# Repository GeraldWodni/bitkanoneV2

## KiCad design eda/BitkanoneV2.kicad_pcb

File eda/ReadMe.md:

EDA
===

KiCad 5 is required to work on this project properly. I have no experience with EDA files in a repo, and how well they merge, so it might be better to request changes in an issue or ask for exclusive access so we do not destroy each others changes ;)

Bus
---

As Ulli suggested, the Bus should be CAN bus. As the schedule is tight a backup plan exists in the schematics, which allows to Bridge the CAN driver and use I2C directly. Note, however that in that case only 1 PCB should have it's pullups populated, as they are on 1k8 which will allow high speeds at 3mA low source current.

https://cdn-reichelt.de/documents/datenblatt/A200/MCP2551_MIC.pdf

Sensor
------

Martin found a nice PCB which holds the BMP280 suggested by Erich and Bernd as well as a Gyro and more. This is called a 10DOF, and can be sourced more or less easily. Boards differ in pin count, but the first 4 pins are always:

1. VIN (wird mit 3.3V gespeist)
2. GND
3. 3V3 (out)
4. SDA
5. SCL

The other pins are ignored.
Ebay: Eckstein

https://store.invensense.com/datasheets/invensense/MPU-6050_DataSheet_V3%204.pdf
https://www.ebay.de/itm/10DOF-Lsm303d-L3gd20-BMP180-Breakout-Modul-Beschleunigungsmesser-Kompass/253091721043?hash=item3aed712f53:g:O0UAAOSw~I5ZjqvM:rk:18:pf:0
https://www.ebay.de/itm/New-SPI-IIC-MPU-9250-MS5611-High-Precision-9-Axis-10DOF-Altitude-sensor-Module/272672204397?hash=item3f7c87a66d:g:fSAAAOSwn-tZGX4T:rk:14:pf:0
https://www.ebay.de/itm/GY-87-10DOF-3-Achsen-Gyroskop-Accelerometer-Sensor-Modul-SE01006/281460524502?hash=item41885ac5d6:g:vKwAAOSwhnlb~pYd:rk:13:pf:0
https://www.reichelt.at/arduino-grove-sensor-imu-10dof-v2-0-grv-imu-10dof-v2-p243392.html?PROVID=2788&gclid=EAIaIQobChMIuNSy9rWQ3wIVhOmaCh0uWwYPEAQYAyABEgIEOfD_BwE&&r=1
https://www.banggood.com/GY-91-MPU9250-BMP280-10DOF-Acceleration-Gyroscope-Compass-Nine-Shaft-Sensor-Module-p-1129541.html?rmmds=search&cur_warehouse=CN

10DOF schematics
http://kom.aau.dk/~jdn/edu/doc/arduino/sensors/gy80gy87gy88/gy87sch.jpg

Motors
------

As there is so little time and much room for error, there is a Motor-Daughterboard connector which will eventually allow to run DC motors via L293D. It's first job is to run Servos instead and allow a Pan/Tilt movement of the Board.

Power
-----

Stand alone boards can be powered via a beefy USB, or can disconnect the solder jumper and supply external Power via X101

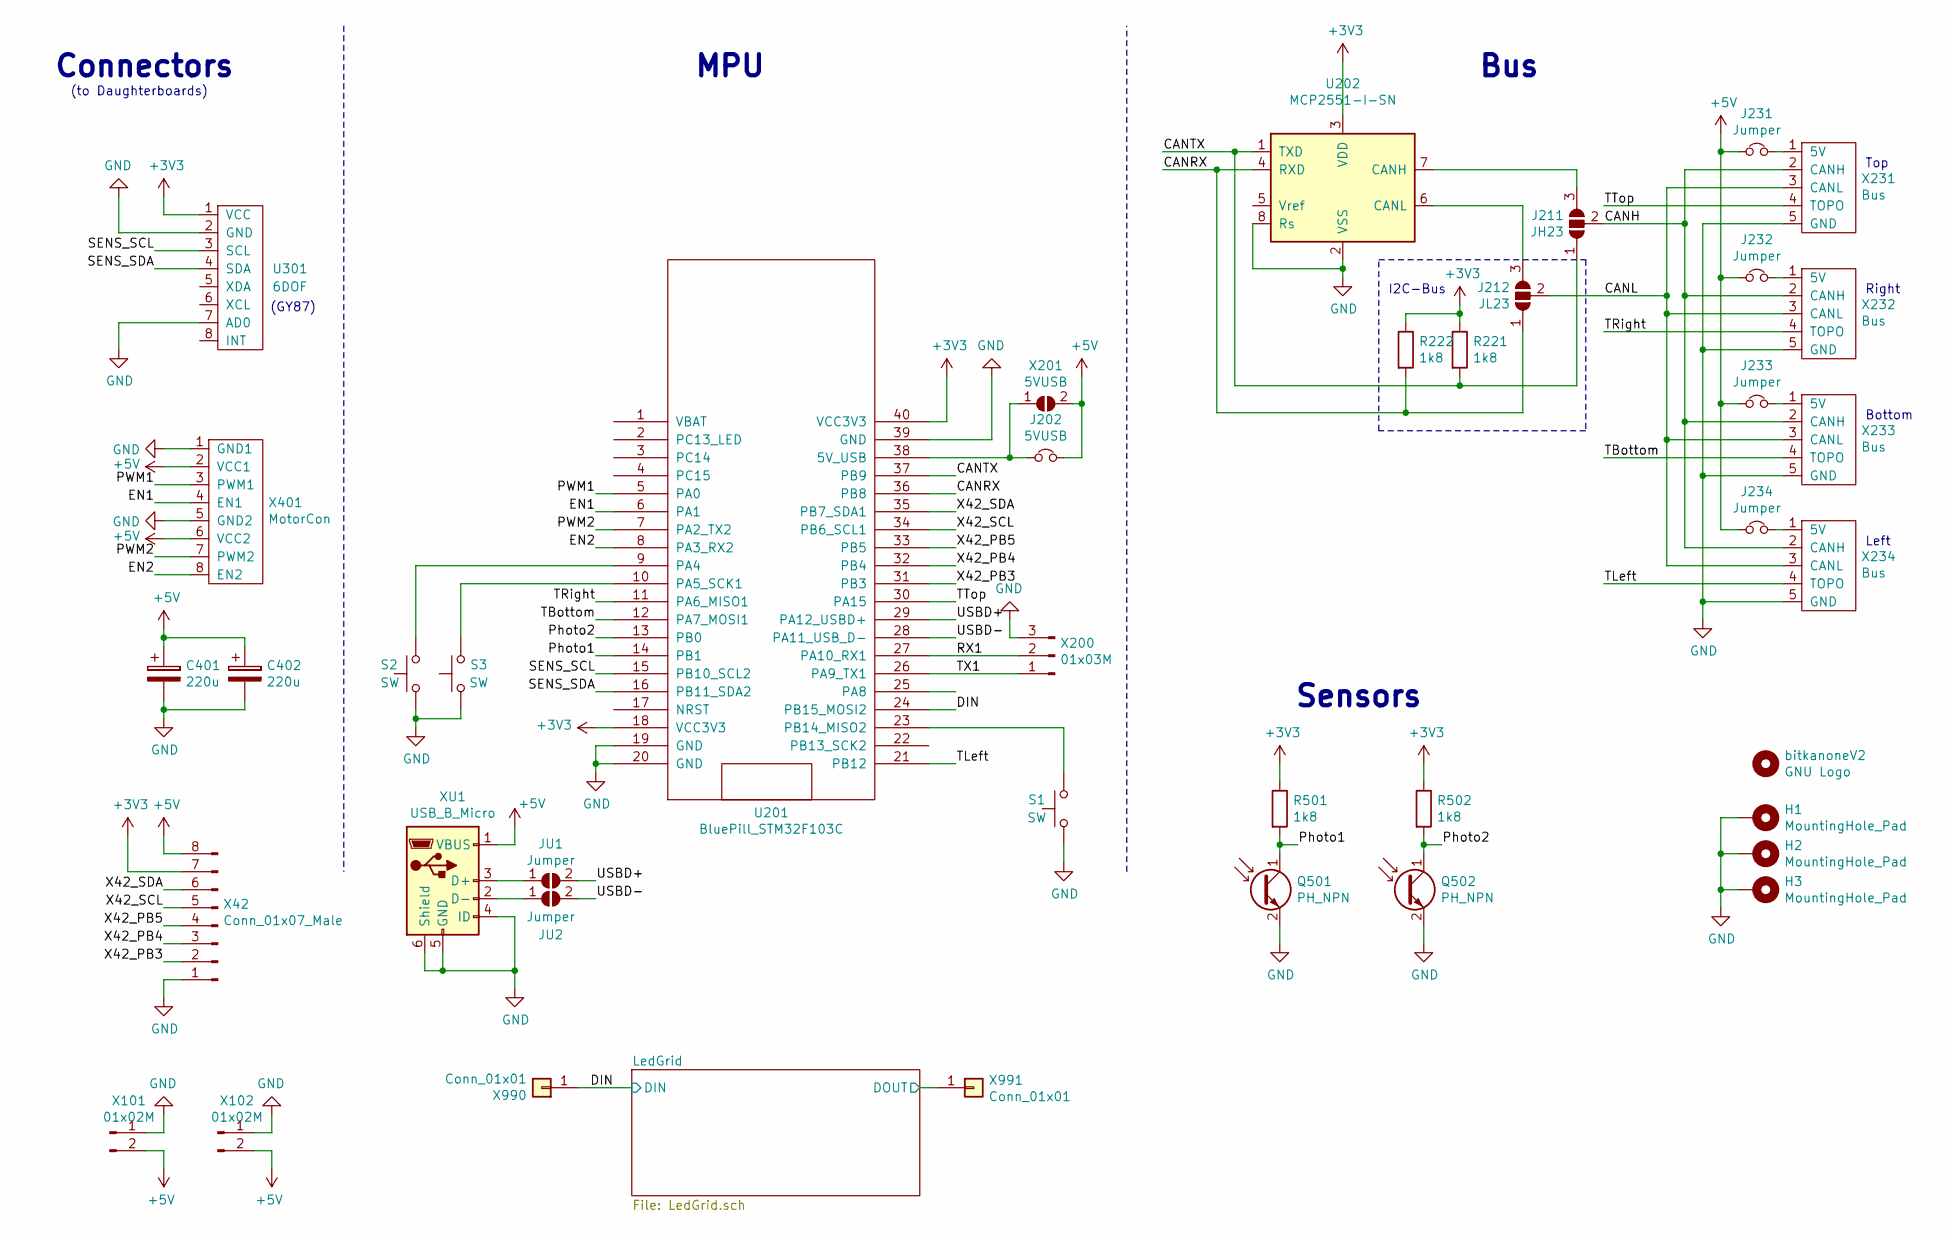
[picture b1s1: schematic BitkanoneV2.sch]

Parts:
C401, C402: 220u; CP_Elec_6.3x5.3
H1, H2, H3: MountingHole_Pad; MountingHole_3.2mm_M3_Pad_Via
J202: 5VUSB; PinSocket_1x02_P2.54mm_Vertical
J211: JH23; SolderJumper-3_P1.3mm_Open_RoundedPad1.0x1.5mm_NumberLabels
J212: JL23; SolderJumper-3_P1.3mm_Open_RoundedPad1.0x1.5mm_NumberLabels
J231, J232, J233, J234: Jumper; SolderJumper-2_P1.3mm_Open_Pad1.0x1.5mm
JU1, JU2: Jumper; SolderJumper-2_P1.3mm_Open_RoundedPad1.0x1.5mm
Q501, Q502: PH_NPN; LED_D3.0mm
R221, R222, R501, R502: 1k8; R_0603_1608Metric_Pad1.05x0.95mm_HandSolder
S1, S2, S3: SW; SW_SPST_FSMSM
U201: BluePill_STM32F103C; BluePill_STM32F103C_Center_NoPROG
U202: MCP2551-I-SN; SOIC-8_3.9x4.9mm_P1.27mm
U301: 6DOF; PinSocket_1x08_P2.54mm_Vertical
X42: Conn_01x07_Male; PinSocket_1x08_P2.54mm_Vertical
X101, X102: 01x02M; PinHeader_1x02_P2.54mm_Vertical
X200: 01x03M; PinHeader_1x03_P2.54mm_Vertical
X201: 5VUSB; SolderJumper-2_P1.3mm_Open_Pad1.0x1.5mm
X231, X232, X233, X234: Bus; PinSocket_1x05_P2.54mm_Vertical
X401: MotorCon; PinSocket_1x08_P2.54mm_Vertical
X990, X991: Conn_01x01; PinHeader_1x01_P2.54mm_Vertical
XU1: USB_B_Micro; USB_Micro-B_Molex-105017-0001
bitkanoneV2: GNU Logo; Symbol_GNU-Logo_SilkscreenTop

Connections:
+3V3: R221.1, R222.1, R501.1, R502.1, U201.18 (VCC3V3), U201.40 (VCC3V3), U202.3 (VDD), U301.1 (VCC), X42.7
+5V: C401.1, C402.1, J202.2, J231.1, J232.1, J233.1, J234.1, X42.8, X101.2, X102.2, X201.2 (B), X401.2 (VCC1), X401.6 (VCC2), XU1.1 (VBUS); also elsewhere on the board
/CANH: J211.2 (C), X231.2 (CANH), X232.2 (CANH), X233.2 (CANH), X234.2 (CANH)
/CANL: J212.2 (C), X231.3 (CANL), X232.3 (CANL), X233.3 (CANL), X234.3 (CANL)
/CANRX: J212.1 (A), R222.2, U201.36 (PB8), U202.4 (RXD)
/CANTX: J211.1 (A), R221.2, U201.37 (PB9), U202.1 (TXD)
/DIN: U201.24 (PB15_MOSI2), X990.1; also elsewhere on the board
/EN1: U201.6 (PA1), X401.4 (EN1)
/EN2: U201.8 (PA3_RX2), X401.8 (EN2)
/LedGrid/DOUT: X991.1; also elsewhere on the board
/PWM1: U201.5 (PA0), X401.3 (PWM1)
/PWM2: U201.7 (PA2_TX2), X401.7 (PWM2)
/Photo1: Q501.1 (C), R501.2, U201.14 (PB1)
/Photo2: Q502.1 (C), R502.2, U201.13 (PB0)
/RX1: U201.27 (PA10_RX1), X200.2
/SENS_SCL: U201.15 (PB10_SCL2), U301.3 (SCL)
/SENS_SDA: U201.16 (PB11_SDA2), U301.4 (SDA)
/TBottom: U201.12 (PA7_MOSI1), X233.4 (TOPO)
/TLeft: U201.21 (PB12), X234.4 (TOPO)
/TRight: U201.11 (PA6_MISO1), X232.4 (TOPO)
/TTop: U201.30 (PA15), X231.4 (TOPO)
/TX1: U201.26 (PA9_TX1), X200.1
/USBD+: JU1.2 (B), U201.29 (PA12_USBD+)
/USBD-: JU2.2 (B), U201.28 (PA11_USB_D-)
/X42_PB3: U201.31 (PB3), X42.2
/X42_PB4: U201.32 (PB4), X42.3
/X42_PB5: U201.33 (PB5), X42.4
/X42_SCL: U201.34 (PB6_SCL1), X42.5
/X42_SDA: U201.35 (PB7_SDA1), X42.6
GND: C401.2, C402.2, H1.1, H2.1, H3.1, Q501.2 (E), Q502.2 (E), S1.1, S2.1, S3.1, U201.19 (GND), U201.20 (GND), U201.39 (GND), U202.2 (VSS), U202.8 (Rs), U301.2 (GND), U301.7 (AD0), X42.1, X101.1, X102.1, X200.3, X231.5 (GND), X232.5 (GND), X233.5 (GND), X234.5 (GND), X401.1 (GND1), X401.5 (GND2), XU1.4 (ID), XU1.5 (GND), XU1.6 (Shield); also elsewhere on the board
unnamed: J202.1, U201.38 (5V_USB), X201.1 (A)
unnamed: J211.3 (B), U202.7 (CANH)
unnamed: J212.3 (B), U202.6 (CANL)
unnamed: J231.2, X231.1 (5V)
unnamed: J232.2, X232.1 (5V)
unnamed: J233.2, X233.1 (5V)
unnamed: J234.2, X234.1 (5V)
unnamed: JU1.1 (A), XU1.3 (D+)
unnamed: JU2.1 (A), XU1.2 (D-)
unnamed: S1.2, U201.23 (PB14_MISO2)
unnamed: S2.2, U201.9 (PA4)
unnamed: S3.2, U201.10 (PA5_SCK1)

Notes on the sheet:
I2C-Bus
Bus
MPU
Connectors
(to Daughterboards)
(GY87)
Left
Bottom
Right
Top
Sensors

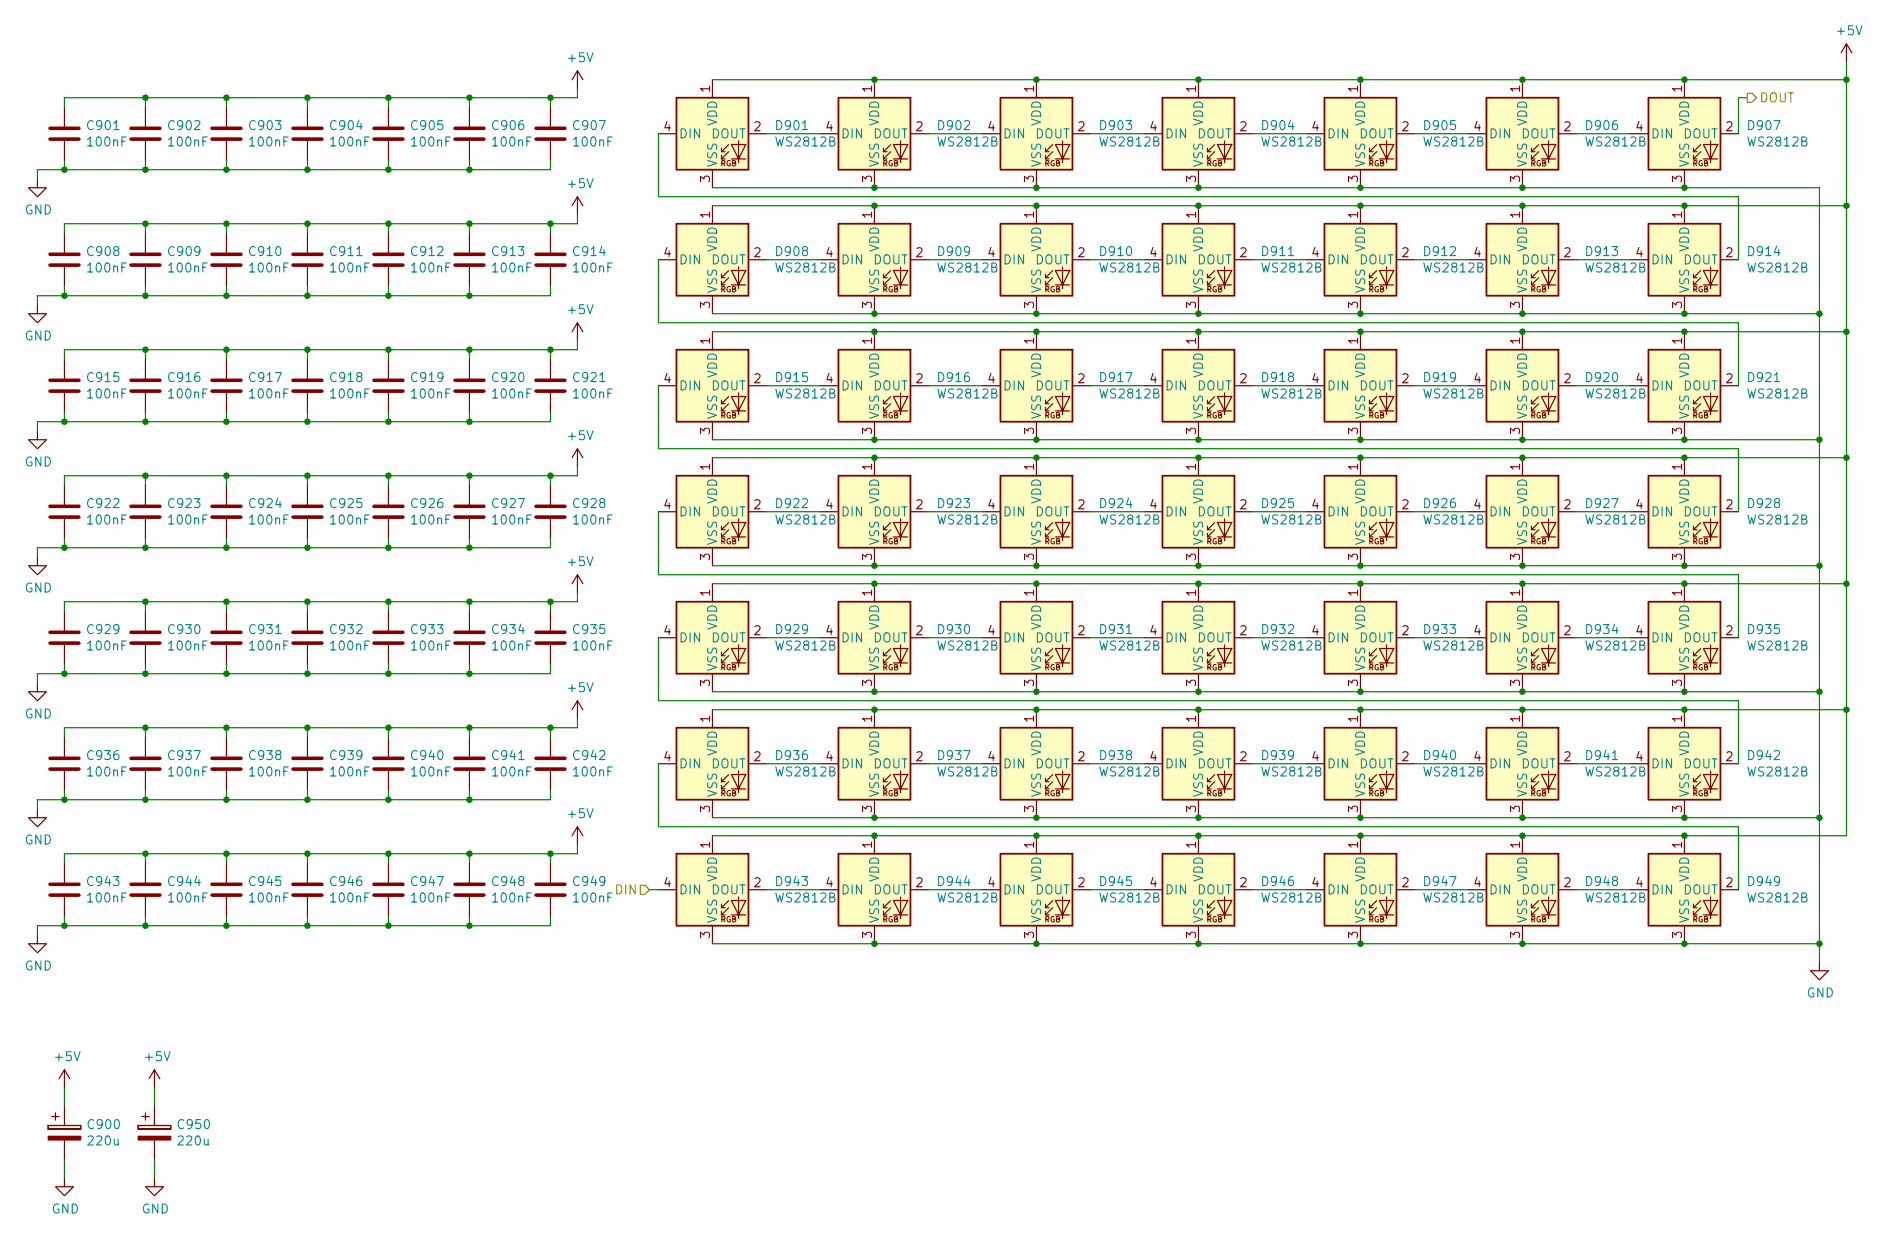
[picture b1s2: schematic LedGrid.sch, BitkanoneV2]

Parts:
C900, C950: 220u; CP_Elec_6.3x5.3
C901, C902, C903, C904, C905, C906, C907, C908, C909, C910, C911, C912, C913, C914, C915, C916, C917, C918, C919, C920, C921, C922, C923, C924, C925, C926, C927, C928, C929, C930, C931, C932, C933, C934, C935, C936, C937, C938, C939, C940, C941, C942, C943, C944, C945, C946, C947, C948, C949: 100nF; C_0603_1608Metric
D901, D902, D903, D904, D905, D906, D907, D908, D909, D910, D911, D912, D913, D914, D915, D916, D917, D918, D919, D920, D921, D922, D923, D924, D925, D926, D927, D928, D929, D930, D931, D932, D933, D934, D935, D936, D937, D938, D939, D940, D941, D942, D943, D944, D945, D946, D947, D948, D949: WS2812B; LED_WS2812B_PLCC4_5.0x5.0mm_P3.2mm

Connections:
+5V: C900.1, C901.1, C902.1, C903.1, C904.1, C905.1, C906.1, C907.1, C908.1, C909.1, C910.1, C911.1, C912.1, C913.1, C914.1, C915.1, C916.1, C917.1, C918.1, C919.1, C920.1, C921.1, C922.1, C923.1, C924.1, C925.1, C926.1, C927.1, C928.1, C929.1, C930.1, C931.1, C932.1, C933.1, C934.1, C935.1, C936.1, C937.1, C938.1, C939.1, C940.1, C941.1, C942.1, C943.1, C944.1, C945.1, C946.1, C947.1, C948.1, C949.1, C950.1, D901.1 (VDD), D902.1 (VDD), D903.1 (VDD), D904.1 (VDD), D905.1 (VDD), D906.1 (VDD), D907.1 (VDD), D908.1 (VDD), D909.1 (VDD), D910.1 (VDD), D911.1 (VDD), D912.1 (VDD), D913.1 (VDD), D914.1 (VDD), D915.1 (VDD), D916.1 (VDD), D917.1 (VDD), D918.1 (VDD), D919.1 (VDD), D920.1 (VDD), D921.1 (VDD), D922.1 (VDD), D923.1 (VDD), D924.1 (VDD), D925.1 (VDD), D926.1 (VDD), D927.1 (VDD), D928.1 (VDD), D929.1 (VDD), D930.1 (VDD), D931.1 (VDD), D932.1 (VDD), D933.1 (VDD), D934.1 (VDD), D935.1 (VDD), D936.1 (VDD), D937.1 (VDD), D938.1 (VDD), D939.1 (VDD), D940.1 (VDD), D941.1 (VDD), D942.1 (VDD), D943.1 (VDD), D944.1 (VDD), D945.1 (VDD), D946.1 (VDD), D947.1 (VDD), D948.1 (VDD), D949.1 (VDD); also elsewhere on the board
/DIN: D943.4 (DIN); also elsewhere on the board
/LedGrid/DOUT: D907.2 (DOUT); also elsewhere on the board
GND: C900.2, C901.2, C902.2, C903.2, C904.2, C905.2, C906.2, C907.2, C908.2, C909.2, C910.2, C911.2, C912.2, C913.2, C914.2, C915.2, C916.2, C917.2, C918.2, C919.2, C920.2, C921.2, C922.2, C923.2, C924.2, C925.2, C926.2, C927.2, C928.2, C929.2, C930.2, C931.2, C932.2, C933.2, C934.2, C935.2, C936.2, C937.2, C938.2, C939.2, C940.2, C941.2, C942.2, C943.2, C944.2, C945.2, C946.2, C947.2, C948.2, C949.2, C950.2, D901.3 (VSS), D902.3 (VSS), D903.3 (VSS), D904.3 (VSS), D905.3 (VSS), D906.3 (VSS), D907.3 (VSS), D908.3 (VSS), D909.3 (VSS), D910.3 (VSS), D911.3 (VSS), D912.3 (VSS), D913.3 (VSS), D914.3 (VSS), D915.3 (VSS), D916.3 (VSS), D917.3 (VSS), D918.3 (VSS), D919.3 (VSS), D920.3 (VSS), D921.3 (VSS), D922.3 (VSS), D923.3 (VSS), D924.3 (VSS), D925.3 (VSS), D926.3 (VSS), D927.3 (VSS), D928.3 (VSS), D929.3 (VSS), D930.3 (VSS), D931.3 (VSS), D932.3 (VSS), D933.3 (VSS), D934.3 (VSS), D935.3 (VSS), D936.3 (VSS), D937.3 (VSS), D938.3 (VSS), D939.3 (VSS), D940.3 (VSS), D941.3 (VSS), D942.3 (VSS), D943.3 (VSS), D944.3 (VSS), D945.3 (VSS), D946.3 (VSS), D947.3 (VSS), D948.3 (VSS), D949.3 (VSS); also elsewhere on the board
unnamed: D901.2 (DOUT), D902.4 (DIN)
unnamed: D901.4 (DIN), D914.2 (DOUT)
unnamed: D902.2 (DOUT), D903.4 (DIN)
unnamed: D903.2 (DOUT), D904.4 (DIN)
unnamed: D904.2 (DOUT), D905.4 (DIN)
unnamed: D905.2 (DOUT), D906.4 (DIN)
unnamed: D906.2 (DOUT), D907.4 (DIN)
unnamed: D908.2 (DOUT), D909.4 (DIN)
unnamed: D908.4 (DIN), D921.2 (DOUT)
unnamed: D909.2 (DOUT), D910.4 (DIN)
unnamed: D910.2 (DOUT), D911.4 (DIN)
unnamed: D911.2 (DOUT), D912.4 (DIN)
unnamed: D912.2 (DOUT), D913.4 (DIN)
unnamed: D913.2 (DOUT), D914.4 (DIN)
unnamed: D915.2 (DOUT), D916.4 (DIN)
unnamed: D915.4 (DIN), D928.2 (DOUT)
unnamed: D916.2 (DOUT), D917.4 (DIN)
unnamed: D917.2 (DOUT), D918.4 (DIN)
unnamed: D918.2 (DOUT), D919.4 (DIN)
unnamed: D919.2 (DOUT), D920.4 (DIN)
unnamed: D920.2 (DOUT), D921.4 (DIN)
unnamed: D922.2 (DOUT), D923.4 (DIN)
unnamed: D922.4 (DIN), D935.2 (DOUT)
unnamed: D923.2 (DOUT), D924.4 (DIN)
unnamed: D924.2 (DOUT), D925.4 (DIN)
unnamed: D925.2 (DOUT), D926.4 (DIN)
unnamed: D926.2 (DOUT), D927.4 (DIN)
unnamed: D927.2 (DOUT), D928.4 (DIN)
unnamed: D929.2 (DOUT), D930.4 (DIN)
unnamed: D929.4 (DIN), D942.2 (DOUT)
unnamed: D930.2 (DOUT), D931.4 (DIN)
unnamed: D931.2 (DOUT), D932.4 (DIN)
unnamed: D932.2 (DOUT), D933.4 (DIN)
unnamed: D933.2 (DOUT), D934.4 (DIN)
unnamed: D934.2 (DOUT), D935.4 (DIN)
unnamed: D936.2 (DOUT), D937.4 (DIN)
unnamed: D936.4 (DIN), D949.2 (DOUT)
unnamed: D937.2 (DOUT), D938.4 (DIN)
unnamed: D938.2 (DOUT), D939.4 (DIN)
unnamed: D939.2 (DOUT), D940.4 (DIN)
unnamed: D940.2 (DOUT), D941.4 (DIN)
unnamed: D941.2 (DOUT), D942.4 (DIN)
unnamed: D943.2 (DOUT), D944.4 (DIN)
unnamed: D944.2 (DOUT), D945.4 (DIN)
unnamed: D945.2 (DOUT), D946.4 (DIN)
unnamed: D946.2 (DOUT), D947.4 (DIN)
unnamed: D947.2 (DOUT), D948.4 (DIN)
unnamed: D948.2 (DOUT), D949.4 (DIN)

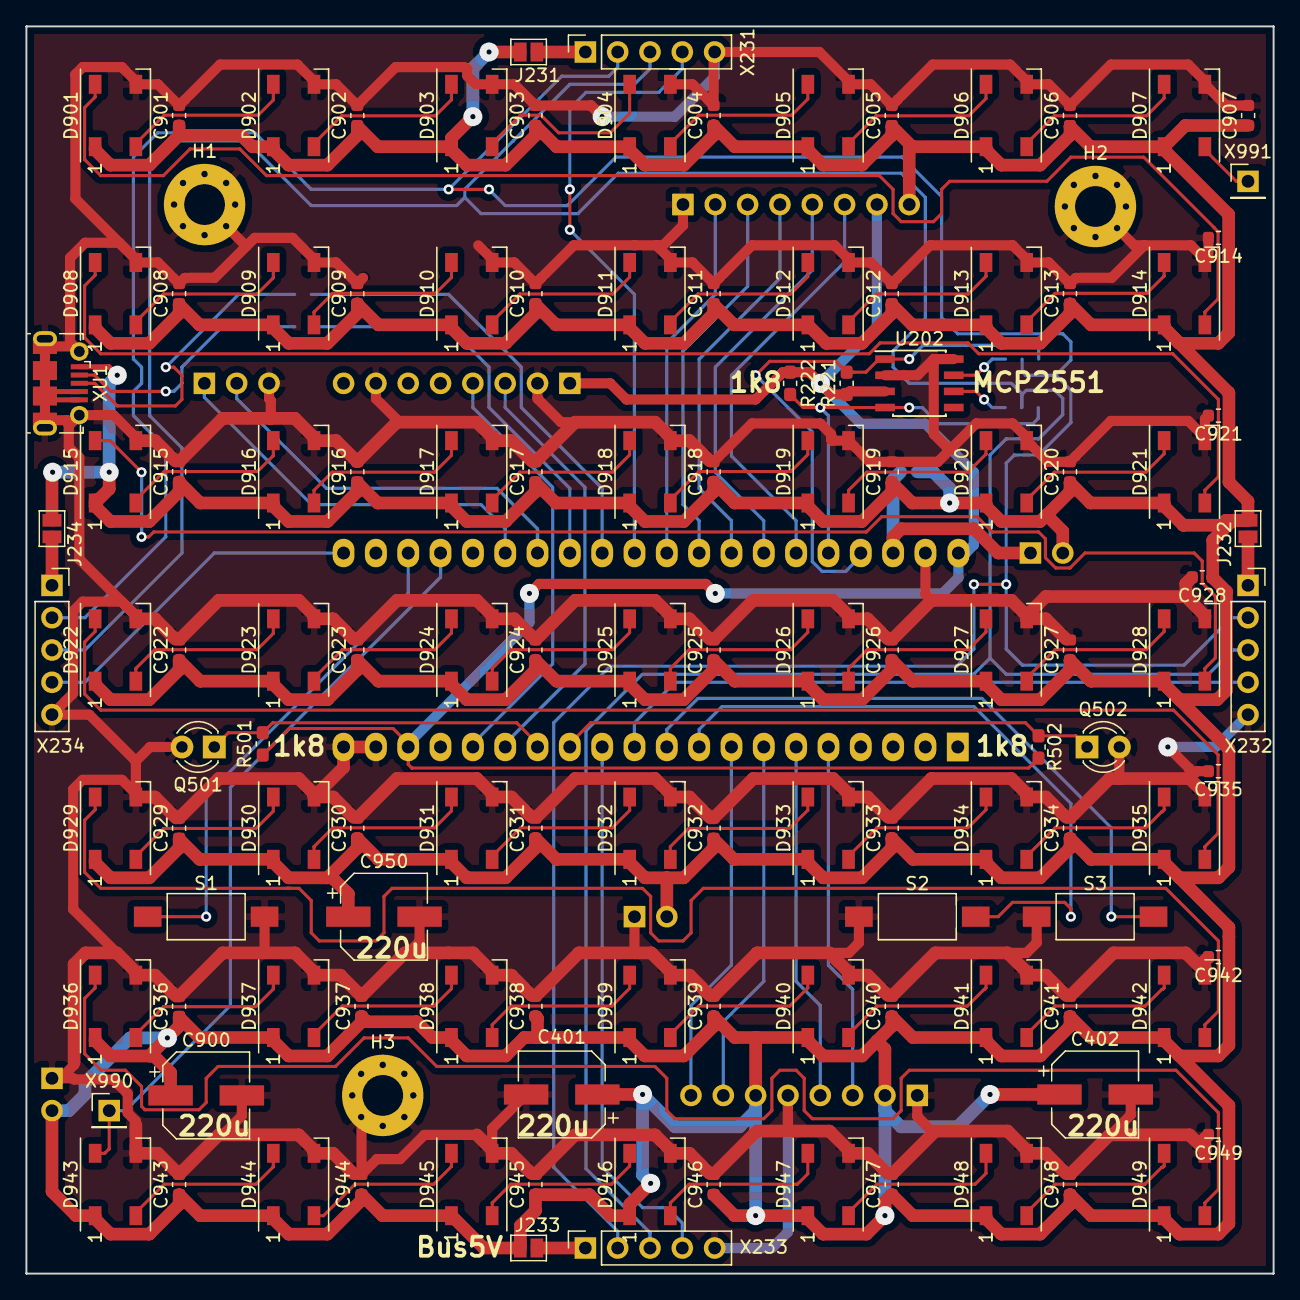
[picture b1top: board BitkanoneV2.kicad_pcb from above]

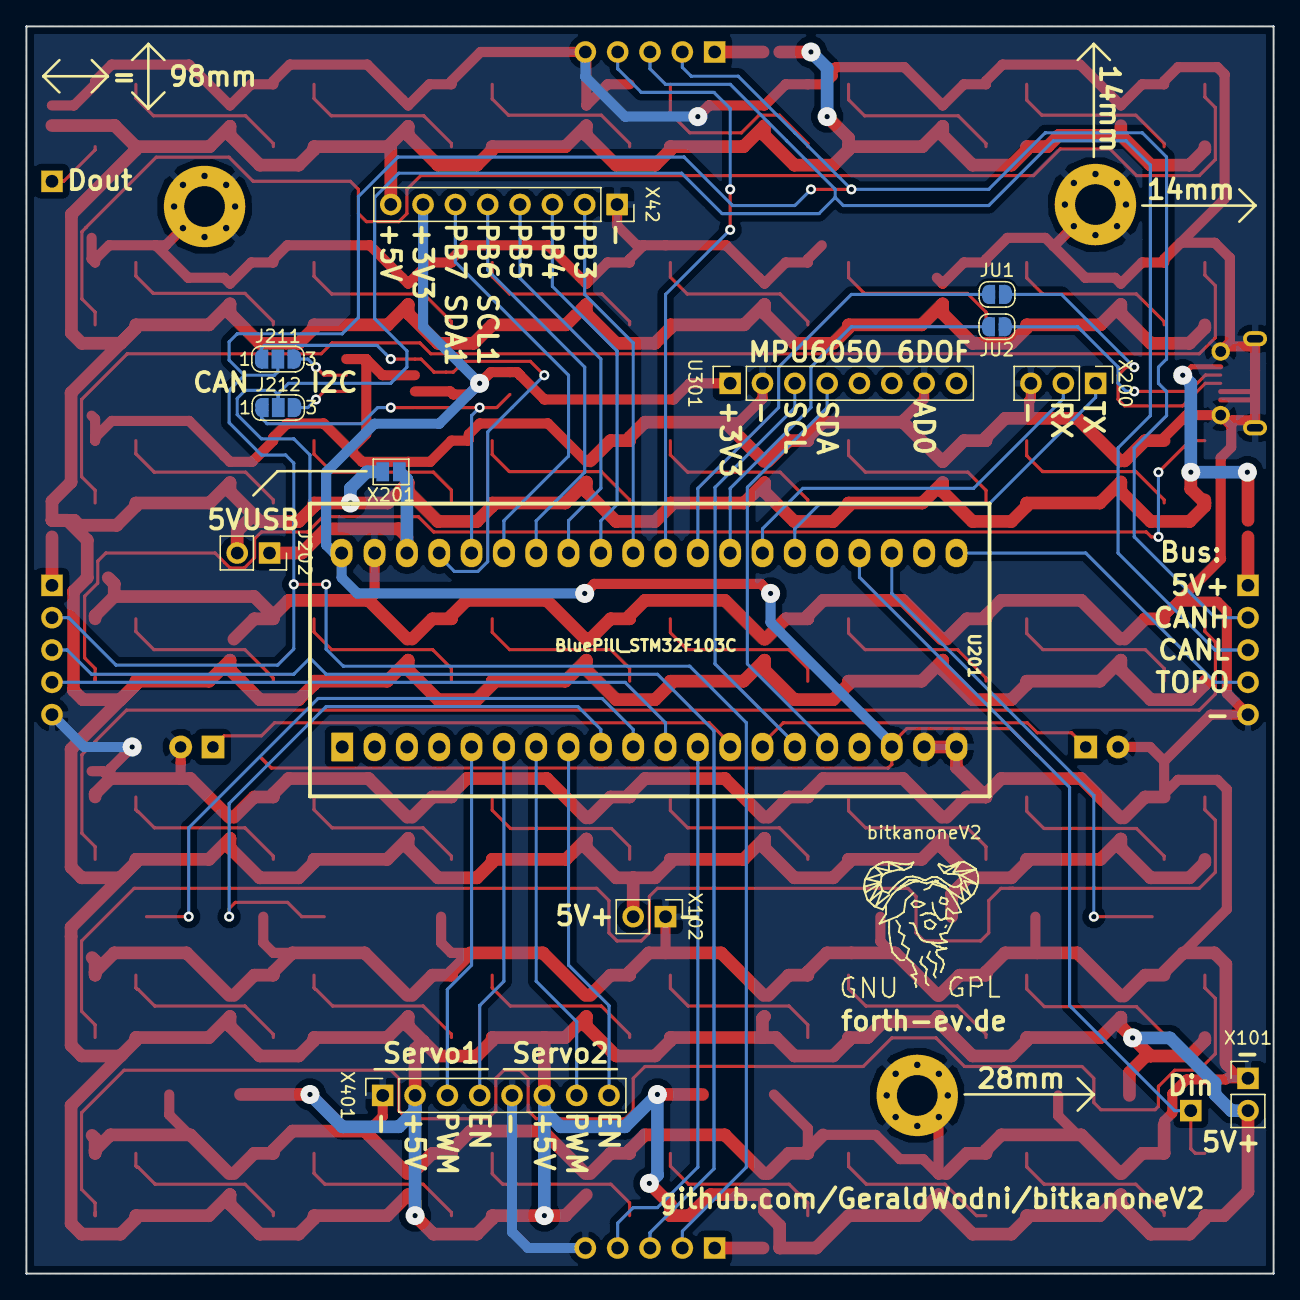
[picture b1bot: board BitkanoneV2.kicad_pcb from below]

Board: 2 copper layers, 98.0 x 98.0 mm, 140 parts (14 on the bottom side), 90 nets.

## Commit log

2018-12-08 Schematic done, needs hierarchy
2018-12-08 WS2812B grid finished
2018-12-09 placement finished
2018-12-09 all but bus routed
2018-12-10 routing finished
2018-12-10 Pdf printouts added
2018-12-11 U301:more space; Phototransistors, Buttons and X42 added
2018-12-11 silk screen documentation added
2018-12-11 Software started, GPIO led can now turn on and off, yay :D
2018-12-12 spi output working
2018-12-12 ws2812b working, port successfull \o/
2018-12-12 USB port added; Mounting holes added; Silk screen measurements added
2018-12-12 bitkanoneV2 first PCB run ordered
2018-12-22 gpio: buttons added; gpio-configure fixed (multiple assignments); led matrix on pcb working
2018-12-22 test added
2018-12-22 I2C scanning works
2018-12-23 software i2c working
2018-12-23 cad: PanTilt started
2018-12-23 i2c-sw: write working
2018-12-23 mpu read working
2018-12-23 pwm working
2018-12-23 only PWM1+2 see to be working, broken attempt
2018-12-24 pwm working on both channels
2018-12-24 pwm integrated in init chain
2018-12-24 test incorporates mpu
2018-12-24 gpio init fixed (pullups enabled)
2018-12-24 pwms (servos) added to test program
2018-12-25 cad: servoArm & servoCross started
2018-12-26 mecrisp load script added
2018-12-26 USB tty driver added from Jean-Claude Wippler
2018-12-26 test script ignoring mpu added
2018-12-27 cad PanTilt printed: top+middle working, bottom still printing
2018-12-27 double bottom for easy printing added
2018-12-27 idname dummy added
2018-12-28 xy buffer added
2018-12-28 app system started
2018-12-28 Fix app-n
2018-12-28 Limits for app-n
2018-12-28 free-ram and free-flash
2018-12-28 Ledcom added to topo pins
2018-12-28 empty app replaced by null-ptr
2018-12-28 apper working
2018-12-28 us and ms delays added; strobe working
2018-12-28 scanner app working
2018-12-28 schematic: ledcom cathode fixed
2018-12-28 apps: scanner movement added
2018-12-28 apper: next-app fixed
2018-12-29 glitter ported
2018-12-29 apps rewritten to forward reference
2018-12-29 demo-appswitcher added
2018-12-29 hsv>rgb added; scanner switches hue (super slow)
2018-12-29 forth app added; glitter random-pan fixed
2018-12-30 balance app started
2018-12-30 balance-app: hysteresis added
2018-12-30 Helmar Wodtke's Wurmi added to apps
2018-12-31 led-nt defered: allows for bis-store
2018-12-31 xy-store out of bounds drop fixed
2018-12-31 rain-app added
2018-12-31 0<= removed from rain; f.fs ignore for local fast include
2018-12-31 fonts started
2019-01-01 rain added to standard apps
2019-01-01 font output filenames fixed to *.fs
2019-01-01 text ported
2019-01-02 text: front blank scroll working
2019-01-03 cursive scroll added and working
2019-01-05 mpu skip added (S3), ledcheck app added
2019-01-06 apps: preliminary logos added, logo switching working
2019-01-06 apper select and run working
2019-01-06 cooler app logos added
2019-01-06 human-presence detected now stylized
2019-01-07 merged newest wurmi version
2019-01-08 turtle started; bresenham working in 1 halfsector
2019-01-08 bresenham cleaned up
2019-01-08 bresenham quadrant wrapper started
2019-04-06 cad: Diffusor added
2019-04-07 testcases removed for faster loading
2019-04-07 Button added (to Diffusor.scad)
2019-04-07 cad: Handheld added
2019-04-07 nompu test simplified, loader added
2019-04-07 cad: ResetButton added to handheld
2019-04-12 5px font fixed; countdown app added
2019-12-28 turtle: bresenham ported from wave(t800 nokia 6610 display) - not yet working
2019-12-28 turtle: bresenham fixed
2019-12-28 turtle: line+ fixed
2019-12-28 text: dc for centered text added
2019-12-29 turtle: fill added
2019-12-29 apps: new demo mode with app skip added
